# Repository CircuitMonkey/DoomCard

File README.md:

# DoomCard
Doom keycard themed PCB

I created a key card styled business card which is insprired by the Door Key Cards found in the original Doom game.

* Features
  * Measures 80mm long x 50mm high.
  * Uses 0402 size parts for a good SMT soldering challenge.
  * Adding recommended components will allow it to run as an Arduino Leonardo clone.
  * All Arduino pins route to a pad.
  * Includes spots for three WS2812B (3535-size) LEDs. Wired from SCK line.
  * Open Source!  Modify and embelish as desired.
  * Made with Eagle CAD

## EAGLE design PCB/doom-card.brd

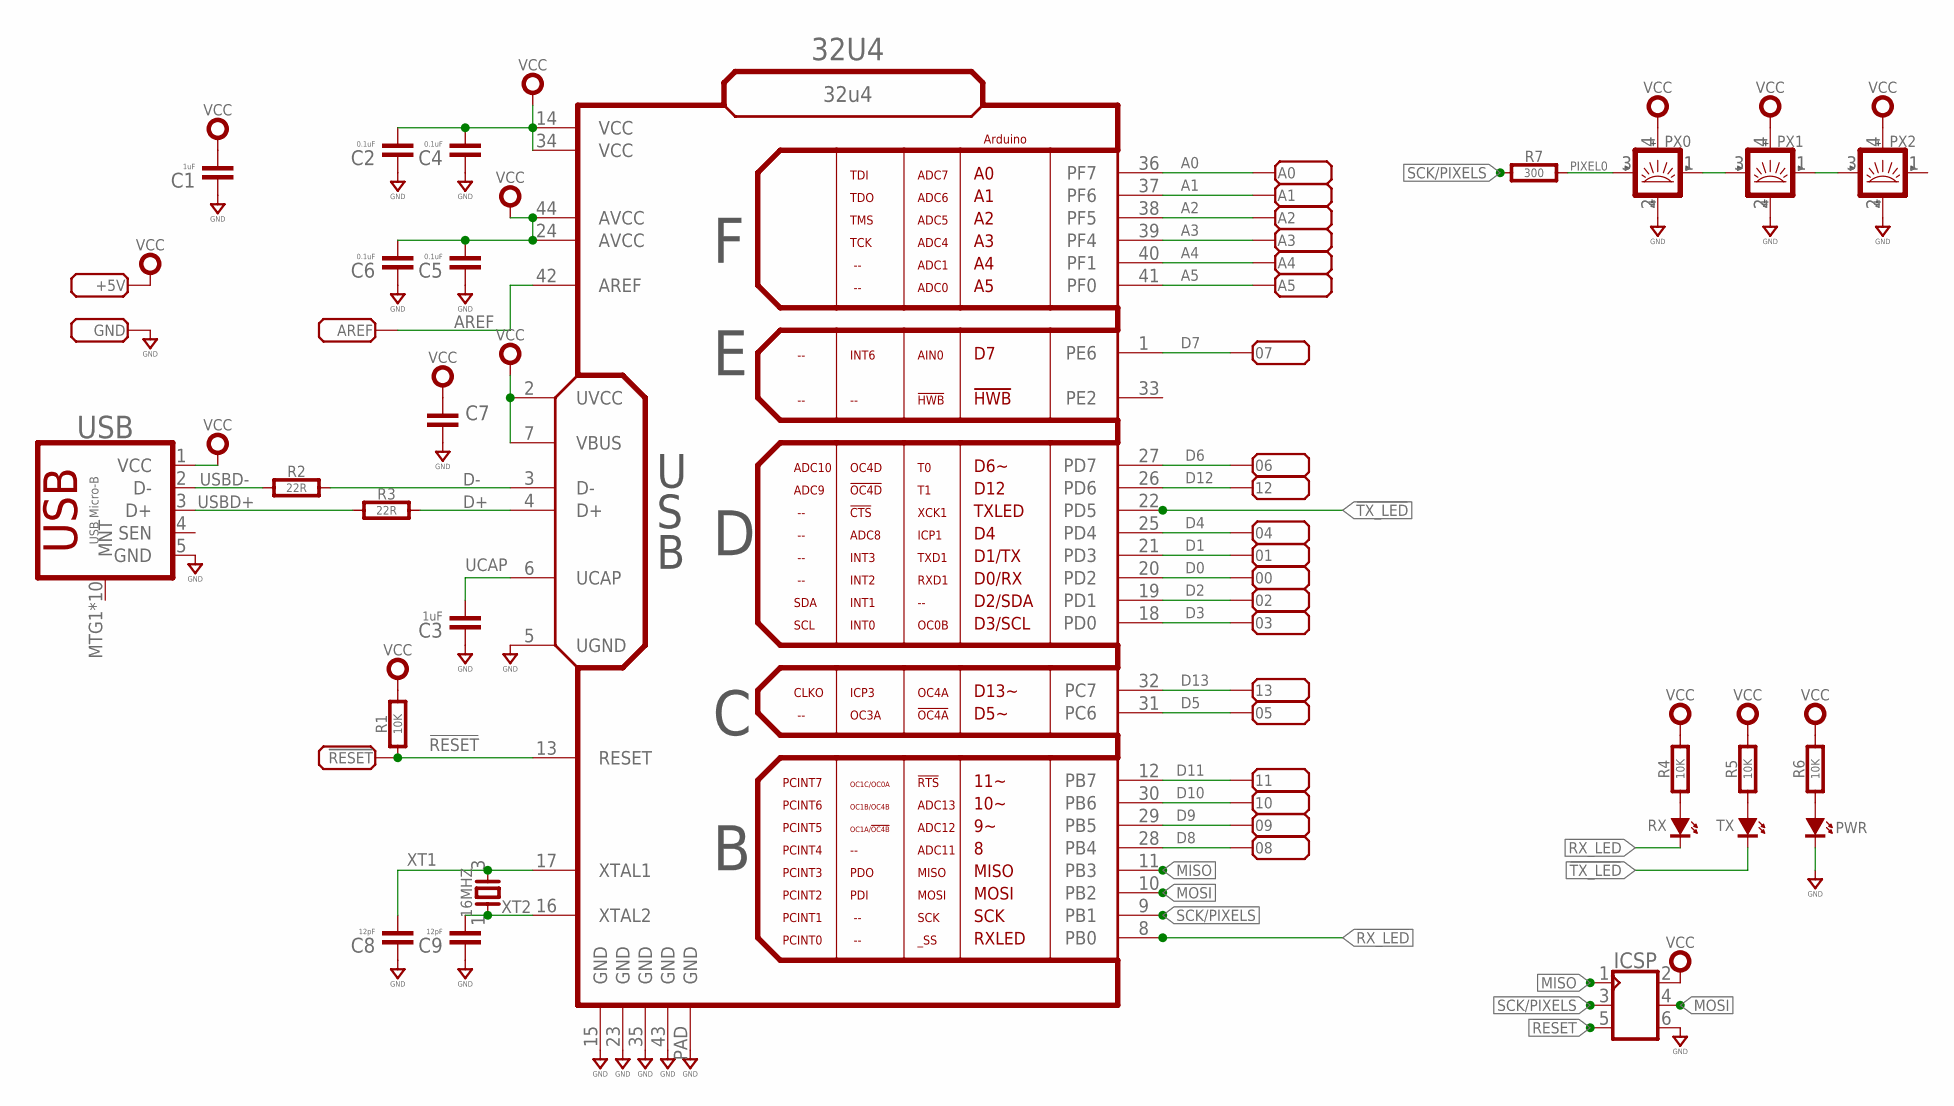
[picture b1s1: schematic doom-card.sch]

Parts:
00, 01, 02, 03, 04, 05, 06, 07, 08, 09, 10, 11, 12, 13: PADSMD-100X100; SMD-100X100
16MHZ: SMD-4P3X5; ABRACON_ABM3C
32U4: 32u4; QFN50P700X700X100-44
!RESET: PADSMD-100X100; SMD-100X100
+5V: PADSMD-100X100; SMD-100X100
A0, A1, A2, A3, A4, A5: PADSMD-100X100; SMD-100X100
AREF: PADSMD-100X100; SMD-100X100
C1, C3: 1uF; 0402-CAP
C2, C4, C5, C6: 0.1uF; 0402-CAP
C7: CAPACITOR0603; 0603-CAP
C8, C9: 12pF; 0402-CAP
GND: PADSMD-100X100; SMD-100X100
ICSP: CON_03X2-VT_SMD; MA03X2-VT-SMD
PWR: SMT0402; SMD_0402
PX0, PX1, PX2: SMART_LED3535; SMD_3535
R1, R4, R5, R6: 10K; 0402-RES
R2, R3: 22R; 0402-RES
R7: 300; 0402-RES
RX: SMT0402; SMD_0402
TX: SMT0402; SMD_0402
USB: USB Micro-B; JAE-DX4R005

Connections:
!RESET: 32U4.13 (RESET), !RESET.PAD, ICSP.5, R1.1
!RX_LED: 32U4.8 (PB0), RX.K (C)
!TX_LED: 32U4.22 (PD5), TX.K (C)
A0: 32U4.36 (PF7), A0.PAD
A1: 32U4.37 (PF6), A1.PAD
A2: 32U4.38 (PF5), A2.PAD
A3: 32U4.39 (PF4), A3.PAD
A4: 32U4.40 (PF1), A4.PAD
A5: 32U4.41 (PF0), A5.PAD
AREF: 32U4.42 (AREF), AREF.PAD
D0: 00.PAD, 32U4.20 (PD2)
D1: 01.PAD, 32U4.21 (PD3)
D2: 02.PAD, 32U4.19 (PD1)
D3: 03.PAD, 32U4.18 (PD0)
D4: 04.PAD, 32U4.25 (PD4)
D5: 05.PAD, 32U4.31 (PC6)
D6: 06.PAD, 32U4.27 (PD7)
D7: 07.PAD, 32U4.1 (PE6)
D8: 08.PAD, 32U4.28 (PB4)
D9: 09.PAD, 32U4.29 (PB5)
D10: 10.PAD, 32U4.30 (PB6)
D11: 11.PAD, 32U4.12 (PB7)
D12: 12.PAD, 32U4.26 (PD6)
D13: 13.PAD, 32U4.32 (PC7)
D+: 32U4.4 (D+), R3.2
D-: 32U4.3 (D-), R2.2
GND: 16MHZ.2 (GND), 16MHZ.4 (GND), 32U4.5 (UGND), 32U4.15 (GND), 32U4.23 (GND), 32U4.35 (GND), 32U4.43 (GND), 32U4.PAD (GND), C1.1, C2.1, C3.1, C4.1, C5.1, C6.1, C7.2, C8.1, C9.1, GND.PAD, ICSP.6, PWR.K (C), PX0.2 (GND), PX1.2 (GND), PX2.2 (GND), USB.5 (GND)
MISO: 32U4.11 (PB3), ICSP.1
MOSI: 32U4.10 (PB2), ICSP.4
unnamed: R4.1, RX.A
unnamed: R5.1, TX.A
unnamed: PWR.A, R6.1
unnamed: PX0.1 (OUT), PX1.3 (IN)
unnamed: PX1.1 (OUT), PX2.3 (IN)
PIXEL0: PX0.3 (IN), R7.2
SCK/PIXELS: 32U4.9 (PB1), ICSP.3, R7.1
UCAP: 32U4.6 (UCAP), C3.2
USBD+: R3.1, USB.3 (D+)
USBD-: R2.1, USB.2 (D-)
VCC: 32U4.2 (UVCC), 32U4.7 (VBUS), 32U4.14 (VCC), 32U4.24 (AVCC), 32U4.34 (VCC), 32U4.44 (AVCC), +5V.PAD, C1.2, C2.2, C4.2, C5.2, C6.2, C7.1, ICSP.2, PX0.4 (VDD), PX1.4 (VDD), PX2.4 (VDD), R1.2, R4.2, R5.2, R6.2, USB.1 (VCC)
XT1: 16MHZ.3, 32U4.17 (XTAL1), C8.2
XT2: 16MHZ.1, 32U4.16 (XTAL2), C9.2

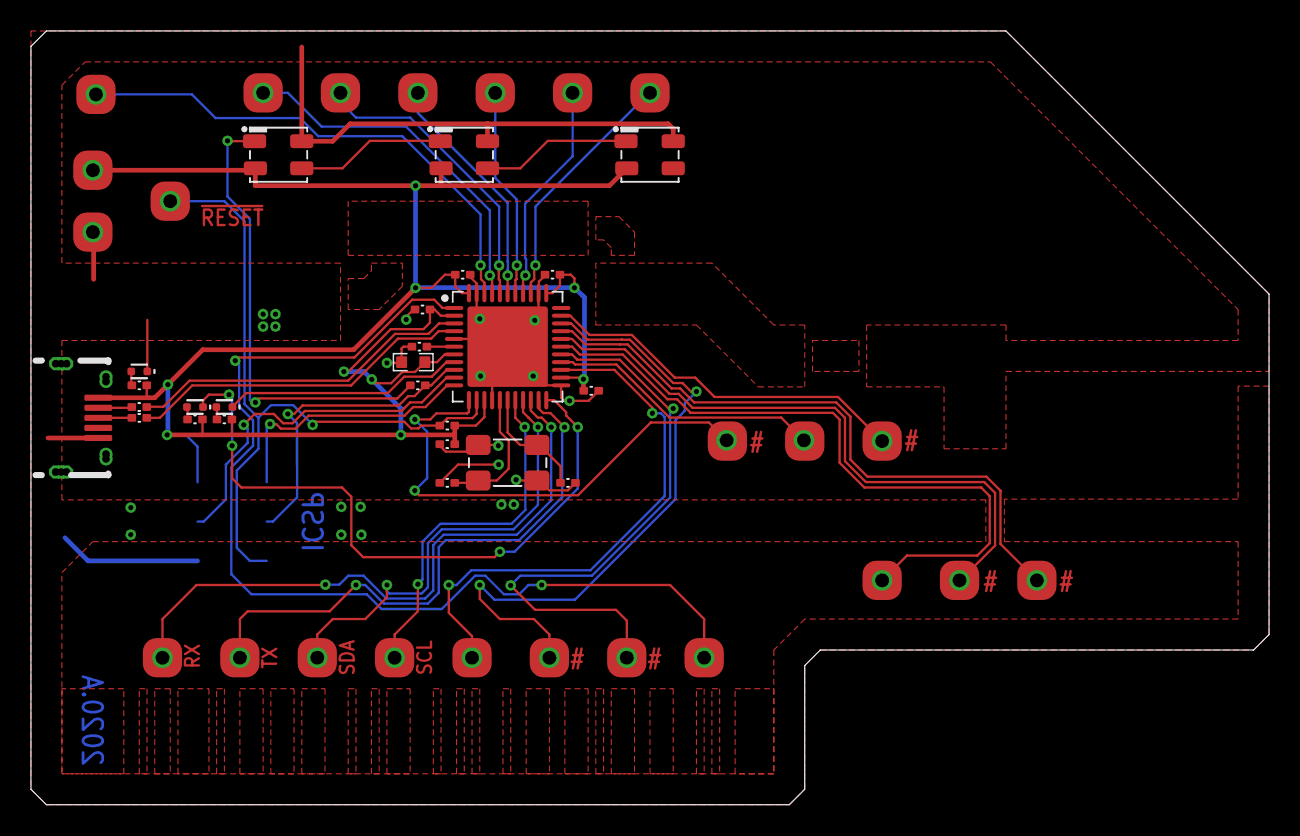
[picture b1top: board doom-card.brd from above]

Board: 2 copper layers, 80.0 x 50.0 mm, 50 parts (1 on the bottom side), 42 nets.

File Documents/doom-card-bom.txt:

Partlist DoomCard Rev. A

Part   Value          Device                     Package              Description               MFR MPN
16MHZ  16MHz          SMD-4P3X5                  ABRACON_ABM3C        Crystal
32U4   32u4           ATMEGA32U4                 QFN-44               ATMEGA 32U4
C1     1uF            CAPACITOR0402              0402-CAP             Capacitor  CAP
C2     0.1uF          CAPACITOR0402              0402-CAP             Capacitor  CAP
C3     1uF            CAPACITOR0402              0402-CAP             Capacitor  CAP
C4     0.1uF          CAPACITOR0402              0402-CAP             Capacitor  CAP
C5     0.1uF          CAPACITOR0402              0402-CAP             Capacitor  CAP
C6     0.1uF          CAPACITOR0402              0402-CAP             Capacitor  CAP
C7     10uF           CAPACITOR0603              0603-CAP             Capacitor  CAP
C8     12pF           CAPACITOR0402              0402-CAP             Capacitor  CAP
C9     12pF           CAPACITOR0402              0402-CAP             Capacitor  CAP
ICSP   HEADER         CON_03X2-VT_SMD            MA03X2-VT-SMD        Header, 3x2 (6-pin), SMT
PX0    WS2812         SMART_LED3535              SMD_3535             Smart LED  SK6812  WS2812
PX1    WS2812         SMART_LED3535              SMD_3535             Smart LED  SK6812  WS2812
PX2    WS2812         SMART_LED3535              SMD_3535             Smart LED  SK6812  WS2812
R1     10K            RESISTOR0402               0402-RES             Resistor
R2     22R            RESISTOR0402               0402-RES             Resistor
R3     22R            RESISTOR0402               0402-RES             Resistor
R4     10K            RESISTOR0402               0402-RES             Resistor
R5     10K            RESISTOR0402               0402-RES             Resistor
R6     10K            RESISTOR0402               0402-RES             Resistor
R7     300            RESISTOR0402               0402-RES             Resistor
PWR    GREEN          SMT0402                    SMD_0402             LED SMT
RX     GREEN          SMT0402                    SMD_0402             LED SMT
TX     BLUE           SMT0402                    SMD_0402             LED SMT
USB    USB Micro-B    USB-B-MICRO-SMTJAE-DX4R005 JAE-DX4R005          USB Micro - B-style      JAE DX4R005JJ2R1800 https://www.mouser.com/ProductDetail/DX4R005JJ2R1800

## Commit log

2019-12-28 First Rev of Doom Card
2019-12-28 Update schematic rev info
    Added screen shots of front and back.
